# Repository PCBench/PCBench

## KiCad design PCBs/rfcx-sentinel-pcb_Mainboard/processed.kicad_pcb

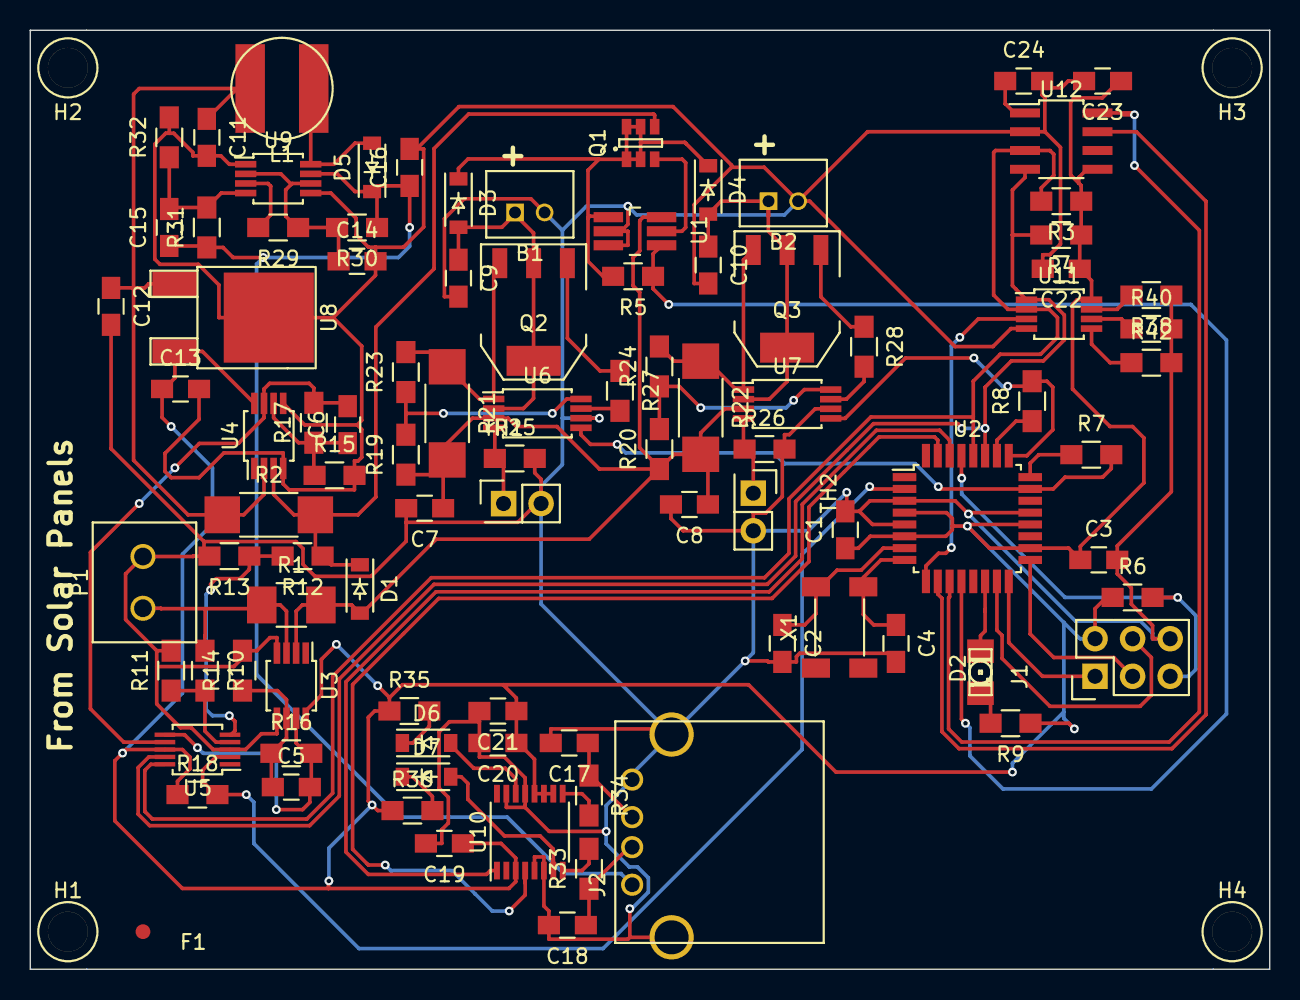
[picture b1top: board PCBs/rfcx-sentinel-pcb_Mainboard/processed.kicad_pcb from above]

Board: 2 copper layers, 83.8 x 63.5 mm, 100 parts (1 on the bottom side), 64 nets.

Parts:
B1, B2: Li-ion(2Cell); JST_BAT
C1, C3, C12, C13, C14: 1uF; C_0805_HandSoldering
C2, C4: 6pF; C_0805_HandSoldering
C5, C6, C7, C8, C9, C10, C22: 0.1uF; C_0805_HandSoldering
C11: 22uF Tant; C_0805_HandSoldering
C15: 39pF; C_0805_HandSoldering
C16: 68uF Tant; C_0805_HandSoldering
C17, C18: 47pF; C_0805_HandSoldering
C19, C20: 100nF; C_0805_HandSoldering
C21: 4.7uF; C_0805_HandSoldering
C23: 0.22uF; C_0805_HandSoldering
C24: 0.1; C_0805_HandSoldering
D1, D3, D4: 1N5819; SOD-123
D2: LED; LED-1206
D5: Diode-Shottky; SOD-123
D6: GRN; SOD-123
D7: LED; SOD-123
F1: Fiducial; Fiducial_1mm_Dia_2.54mm_Outer_CopperTop
H1, H2, H3, H4: Mounting_Hole; Mnt_Hole
J1: ICSP; Pin_Header_Straight_2x03
J2: USB; USB_A
L1: 6.8uH; Ind_6x6
Noname_1: Symbol_OSHW-Logo_SilkScreen
P1: CONN_01X02; TerminalBlock_2
Q1: FDC638; FDC-SOT-23-6
Q2, Q3: FZT788B; SOT-223
R1: Res; R_1210_HandSoldering
R2: 0.5,1W; R_2010_HandSoldering
R3, R4, R6, R18, R19, R20, R38, R40, R42: 10k; R_0805_HandSoldering
R5: 470k; R_0805_HandSoldering
R7, R8, R27, R28: 1k; R_0805_HandSoldering
R9, R35, R36: 730; R_0805_HandSoldering
R10, R12: 1540; R_0805_HandSoldering
R11, R13: 2100; R_0805_HandSoldering
R14, R15, R29: 200k; R_0805_HandSoldering
R16: 2550; R_0805_HandSoldering
R17: Res; R_0805_HandSoldering
R21, R22: 0.2, 1W; R_2010_HandSoldering
R23, R24: 5k; R_0805_HandSoldering
R25, R26, R32: 49.9k; R_0805_HandSoldering
R30: 49.9; R_0805_HandSoldering
R31: 150k; R_0805_HandSoldering
R33, R34: 27; R_0805_HandSoldering
TH1, TH2: NTC; Pin_Header_Straight_2x01
U1: LTC4412; TSOT-6-MK06A_Handsoldering
U2: ATmega328P; TQFP-32_7x7mm_Pitch0.8mm
U3, U4: LTC6800; MSOP-8_3x3mm_Pitch0.65mm
U5: ADS1015; MSOP-10_3x3mm_Pitch0.5mm
U6, U7: bq2057CTS; TSSOP-8_4.4x3mm_Pitch0.65mm
U8: SM72238; DPAK-2
U9: LMR61428; MSOP-8_3x3mm_Pitch0.65mm
U10: FT230X; SSOP-16_3.9x4.9mm_Pitch0.635mm
U11: LM75BDP; MSOP-8_3x3mm_Pitch0.65mm
U12: HIH6130; HIH-SOIC-8
X1: 32kHz; SOJ-4

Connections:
+3V3: C1.1, C3.1, C13.1, C19.1, C20.1, C21.1, C22.1, C23.1, J1.2, R3.1, R4.1, R6.1, R9.1, R18.1, R35.1, R36.1, U2.4, U2.6, U2.18, U2.20, U3.8, U4.8, U5.8, U8.3, U10.3, U10.10, U10.11, U10.12, U11.8, U12.8
+5V: C15.1, C16.1, D5.1, J2.1, R30.1, R31.1, U9.7
/+3.3V and +5V Regulation/LM_FB: C15.2, R31.2, R32.1, U9.4
/ADC/Input-Current-H: P1.1, R1.1, R10.1, U3.3
/ADC/Input-Current-L: C7.1, C8.1, D1.2, R1.2, R19.1, R20.1, R21.2, R22.2, U1.6, U3.2, U6.3, U7.3
/ADC/Output-Current-H: D1.1, Q1.3, R2.2, R12.1, U4.3
/ADC/Output-Current-L: C11.1, C12.1, L1.1, R2.1, U4.2, U8.1
/Battery Management/Battery-Vout: D3.1, D4.1, Q1.1, R5.2, U1.1
/Environment Sensors/ENV_AL_H: U2.11, U12.5
/Environment Sensors/ENV_AL_L: U2.10, U12.6
/Environment Sensors/ENV_OS: U2.9, U11.3
/Microcontroller/AT-Alert: R18.2, U2.2, U5.2
/Microcontroller/AT-BAT1-STAT: R7.2, U2.23, U6.5
/Microcontroller/AT-BAT2-STAT: R8.2, U2.25, U7.5
/Microcontroller/AT-RXD: U2.30, U10.1
/Microcontroller/AT-SCL: R3.2, U2.28, U5.10, U11.2, U12.3
/Microcontroller/AT-SDA: R4.2, U2.27, U5.9, U11.1, U12.4
/Microcontroller/AT-TXD: U2.31, U10.4
/Microcontroller/PPM_STAT: R5.1, U1.4, U2.12
GND: B1.2, B2.2, C1.2, C2.2, C3.2, C4.2, C7.2, C8.2, C9.2, C10.2, C11.2, C12.2, C13.2, C14.2, C16.2, C17.2, C18.2, C19.2, C20.2, C21.2, C22.2, C23.2, C24.2, J1.6, J2.4, J2.5, P1.2, R11.2, R13.2, R14.2, R15.2, R25.2, R26.2, R32.2, R38.1, R40.2, R42.2, TH1.2, TH2.2, U1.2, U1.3, U2.3, U2.5, U2.21, U3.4, U3.5, U4.4, U4.5, U5.3, U6.6, U7.6, U8.2, U9.1, U9.5, U10.5, U10.6, U10.13, U10.15, U11.4, U12.2
unnamed: B1.1, C9.1, D3.2, Q2.2, Q2.4, U6.2
unnamed: B2.1, C10.1, D4.2, Q3.2, Q3.4, U7.2
unnamed: C2.1, U2.7, X1.1
unnamed: C4.1, U2.8, X1.4
unnamed: C5.1, R14.1, R16.1, U3.6
unnamed: C5.2, R16.2, U3.7, U5.6
unnamed: C6.1, R15.1, R17.1, U4.6
unnamed: C6.2, R17.2, U4.7, U5.7
unnamed: C14.1, R29.1, R30.2, U9.2, U9.6
unnamed: C17.1, J2.3, R34.1
unnamed: C18.1, J2.2, R33.1
unnamed: C24.1, U12.1
unnamed: D2.1, R9.2
unnamed: D2.2, U2.14
unnamed: D5.2, L1.2, U9.8
unnamed: D6.1, R35.2
unnamed: D6.2, U10.14
unnamed: D7.1, R36.2
unnamed: D7.2, U10.7
unnamed: J1.1, U2.16
unnamed: J1.3, U2.17
unnamed: J1.4, U2.15
unnamed: J1.5, R6.2, U2.29
unnamed: Q1.2, U1.5
unnamed: Q2.1, R27.1
unnamed: Q2.3, R21.1, R23.2, U6.1
unnamed: Q3.1, R28.1
unnamed: Q3.3, R22.1, R24.2, U7.1
unnamed: R7.1, U2.24
unnamed: R8.1, U2.26
unnamed: R10.2, R11.1, U5.4
unnamed: R12.2, R13.1, U5.5
unnamed: R19.2, R23.1, U6.8
unnamed: R20.2, R24.1, U7.8
unnamed: R25.1, TH1.1, U6.4
unnamed: R26.1, TH2.1, U7.4
unnamed: R27.2, U6.7
unnamed: R28.2, U7.7
unnamed: R29.2, U9.3
unnamed: R33.2, U10.8
unnamed: R34.2, U10.9
unnamed: R38.2, U11.7
unnamed: R40.1, U11.6
unnamed: R42.1, U11.5

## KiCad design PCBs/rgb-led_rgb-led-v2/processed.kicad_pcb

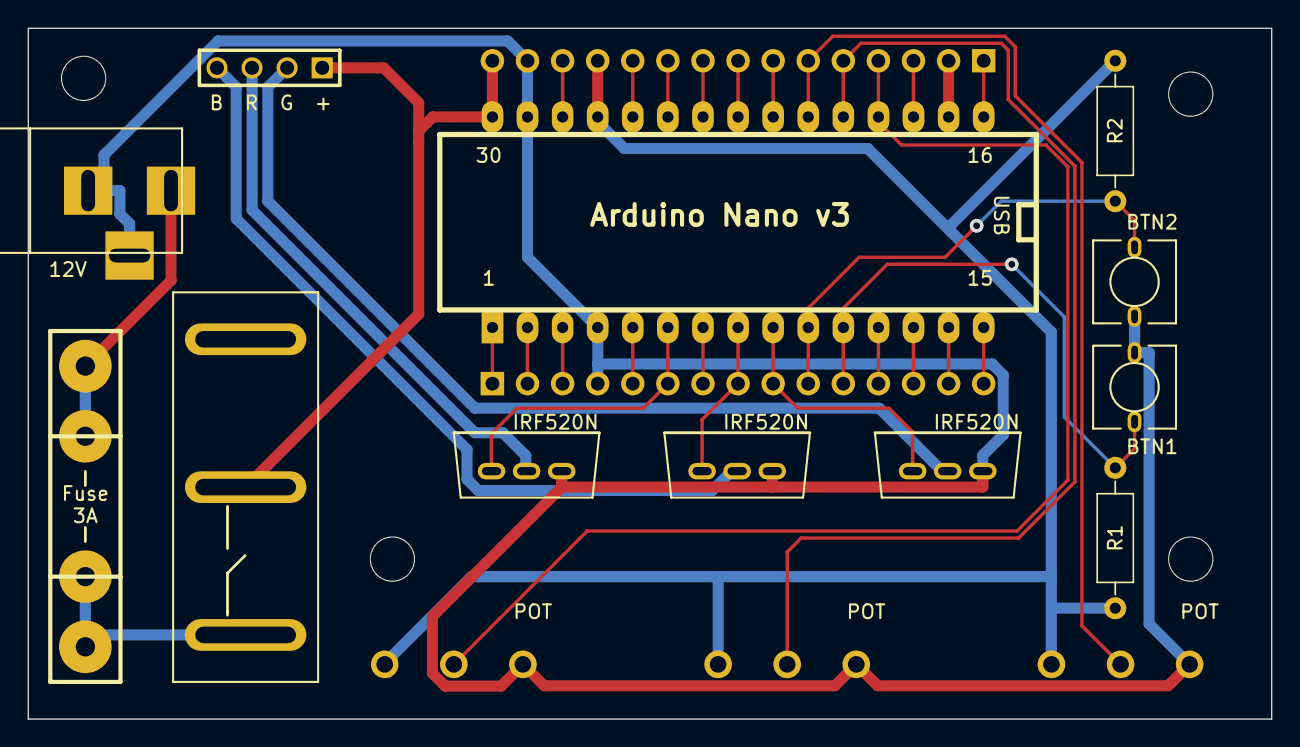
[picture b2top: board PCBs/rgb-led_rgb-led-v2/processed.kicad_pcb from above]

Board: 2 copper layers, 90.0 x 50.0 mm, 17 parts (0 on the bottom side), 34 nets.

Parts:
BTN1, BTN2: SPST; PUSHBUTTON_TS044S
CON1: BARREL_JACK
CONN1: RGB LED; PIN_ARRAY_4x1
F1: FUSE; FUSE5-20
P1, P2: CONN_01X15; Pin_Header_Straight_1x15_Pitch2.54mm_Noborder
QB1: IRF520N FET; IRF520N
QG1: IRF520N FET; IRF520N
QR1: IRF520N FET; IRF520N
R1, R2: R; R_Axial_DIN0207_L6.3mm_D2.5mm_P10.16mm_Horizontal
RV1: POT; POT_3
RV2, RV3: POT; POT_3_Naked
SW1: SPST; KCD3
UC1: ARDUINO_NANO; arduino_nano

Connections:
3.3V: P1.2, UC1.2
5V: P1.12, R1.2, R2.2, RV1.1, RV2.1, RV3.1, UC1.12
A1: P1.1, UC1.1
A3: P1.3, UC1.3
A4: P1.4, RV1.2, UC1.4
A5: P1.5, RV2.2, UC1.5
A6: P1.6, RV3.2, UC1.6
A7: P1.7, UC1.7
A8: P1.8, UC1.8
A9: P1.9, UC1.9
A10: P1.10, UC1.10
A11: P1.11, UC1.11
A13: P1.13, UC1.13
A16: P2.1, UC1.16
A17: P2.2, UC1.17
A18: P2.3, UC1.18
A20: P2.5, UC1.20
A21: P2.6, QR1.G, UC1.21
A22: P2.7, UC1.22
A23: P2.8, QB1.G, UC1.23
A24: P2.9, QG1.G, UC1.24
A25: BTN2.1, P2.10, R2.1, UC1.25
A26: BTN1.1, P2.11, R1.1, UC1.26
A27: P2.12, UC1.27
A28: P2.13, UC1.28
A29: P2.14, UC1.29
A30: P2.15, UC1.30
GND: BTN1.2, BTN2.2, CON1.2, CON1.3, P1.14, P2.4, QB1.S, QG1.S, QR1.S, RV1.3, RV2.3, RV3.3, UC1.14, UC1.19
unnamed: CON1.1, F1.1
unnamed: CONN1.2, QG1.D
unnamed: CONN1.3, QR1.D
unnamed: CONN1.4, QB1.D
unnamed: F1.2, SW1.1
VIN: CONN1.1, P1.15, SW1.2, UC1.15

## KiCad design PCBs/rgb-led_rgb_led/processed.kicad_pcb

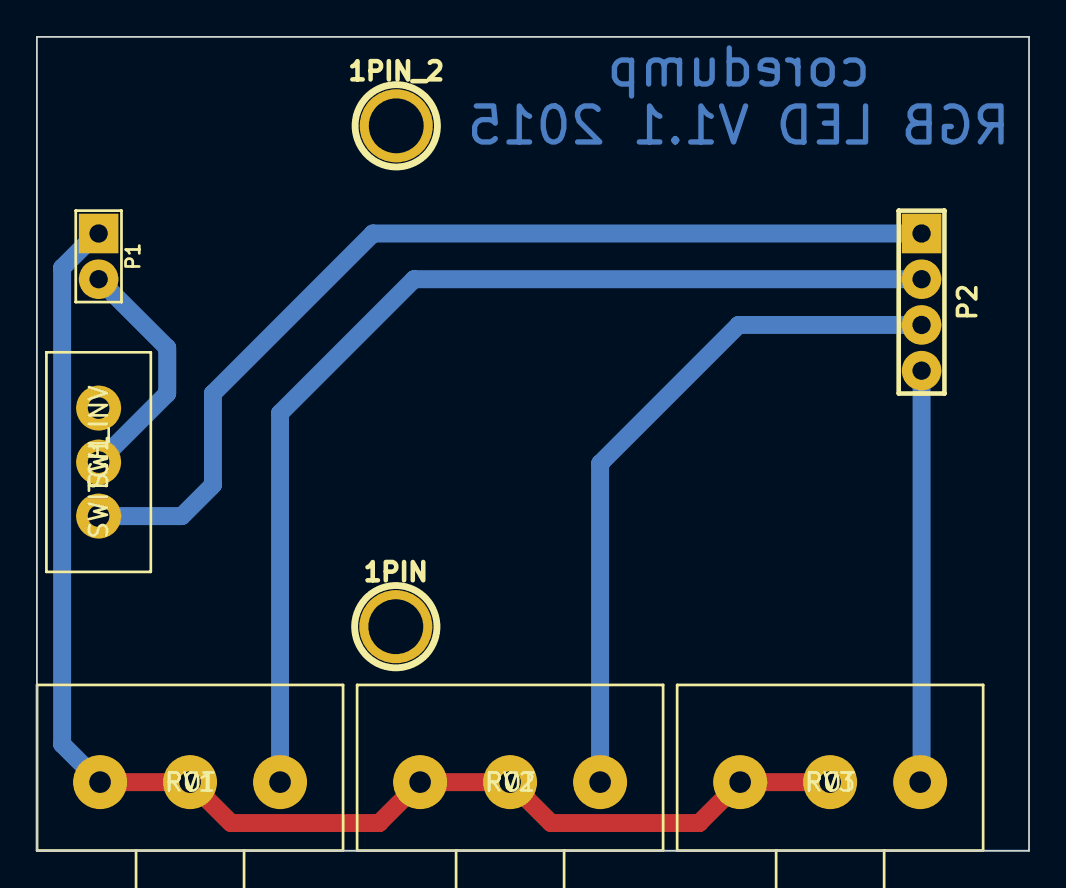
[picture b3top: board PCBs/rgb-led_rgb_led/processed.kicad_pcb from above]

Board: 2 copper layers, 55.1 x 45.2 mm, 9 parts (1 on the bottom side), 6 nets.

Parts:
1PIN, 1PIN_2: P***; 1pin
Noname_1: OSHW_COPPER_10MM
P1: CONN_2; PIN_ARRAY_2X1_THICK
P2: CONN_4; PIN_ARRAY_4x1_THICK
RV1, RV2, RV3: POT; POT_3_THICK
SW1: SWITCH_INV; Switch_SS-12F46

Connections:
GND: P1.1, RV1.1, RV1.2, RV2.1, RV2.2, RV3.1, RV3.2
unnamed: P2.4, RV3.3
unnamed: P2.3, RV2.3
unnamed: P2.2, RV1.3
unnamed: P2.1, SW1.1
VDD: P1.2, SW1.2

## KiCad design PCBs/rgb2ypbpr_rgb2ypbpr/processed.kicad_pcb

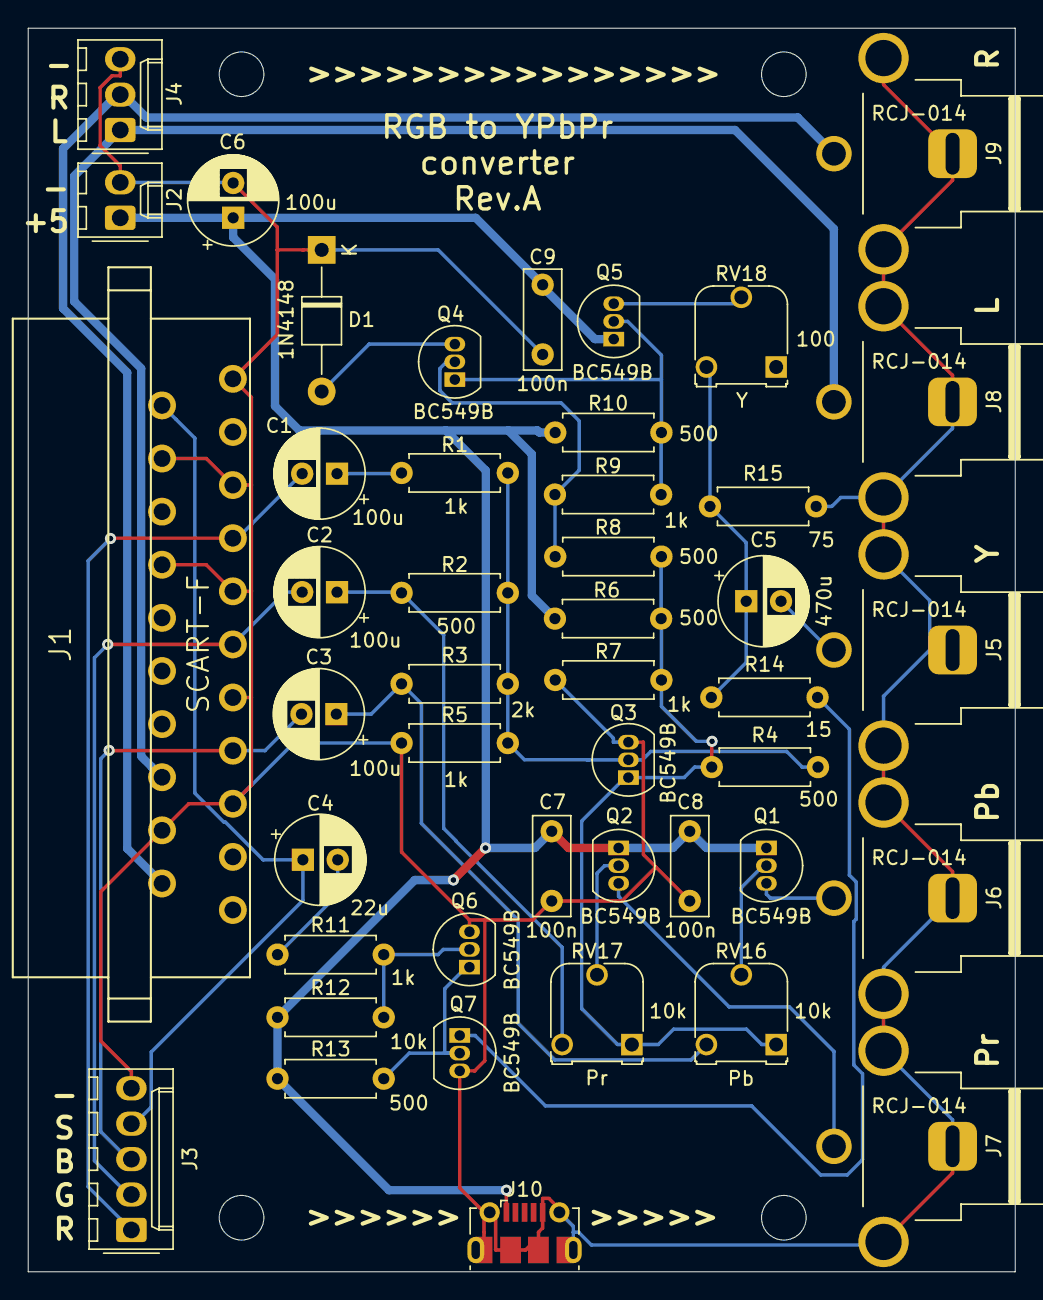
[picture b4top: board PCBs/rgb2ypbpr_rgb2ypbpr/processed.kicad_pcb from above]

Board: 2 copper layers, 70.8 x 89.2 mm, 49 parts (0 on the bottom side), 27 nets.

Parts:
C1, C2, C3, C6: 100u; CP_Radial_D6.3mm_P2.50mm
C4: 22u; CP_Radial_D6.3mm_P2.50mm
C5: 470u; CP_Radial_D6.3mm_P2.50mm
C7, C8, C9: 100n; C_Disc_D7.0mm_W2.5mm_P5.00mm
D1: 1N4148; D_T-1_P10.16mm_Horizontal
H1, H2, H3, H4: MountingHole; MountingHole_3.2mm_M3
J1: SCART-F; SCART
J2: Conn_01x02; Molex_KK-254_AE-6410-02A_1x02_P2.54mm_Vertical
J3: Conn_01x05; Molex_KK-254_AE-6410-05A_1x05_P2.54mm_Vertical
J4: Conn_01x03; Molex_KK-254_AE-6410-03A_1x03_P2.54mm_Vertical
J5, J6, J7, J8, J9: RCJ-014; CUI_RCJ-01X-WIDE
J10: USB_B_Micro; USB_Micro-B_Molex-105017-0001
Q1, Q2, Q3, Q4, Q5, Q6, Q7: BC549B; TO-92_Inline
R1, R5, R7, R9, R11: 1k; R_Axial_DIN0207_L6.3mm_D2.5mm_P7.62mm_Horizontal
R2, R4, R6, R8, R10, R13: 500; R_Axial_DIN0207_L6.3mm_D2.5mm_P7.62mm_Horizontal
R3: 2k; R_Axial_DIN0207_L6.3mm_D2.5mm_P7.62mm_Horizontal
R12: 10k; R_Axial_DIN0207_L6.3mm_D2.5mm_P7.62mm_Horizontal
R14: 15; R_Axial_DIN0207_L6.3mm_D2.5mm_P7.62mm_Horizontal
R15: 75; R_Axial_DIN0207_L6.3mm_D2.5mm_P7.62mm_Horizontal
RV16, RV17: 10k; Potentiometer_Runtron_RM-065_Vertical
RV18: 100; Potentiometer_Runtron_RM-065_Vertical

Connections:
+5V: C6.1, C7.1, C8.1, C9.2, J2.1, J10.1, Q1.1, Q2.1, Q5.1, R6.2, R10.1, R12.2, R13.2
Audio_L: J1.6, J4.1, J8.1
Audio_R: J1.2, J4.2, J9.1
B_IN: C3.2, J1.7, J3.3
CSYNC_IN: C4.1, J1.20, J3.4
GND: C6.2, C7.2, C8.2, C9.1, D1.1, J1.4, J1.5, J1.9, J1.13, J1.14, J1.17, J1.18, J1.21, J2.2, J3.5, J4.3, J5.2, J6.2, J7.2, J8.2, J9.2, J10.5, J10.6, Q3.3, Q6.3, Q7.3, R5.2, R7.1, R15.2
G_IN: C2.2, J1.11, J3.2
unnamed: C1.1, R1.2
unnamed: C2.1, R2.2, RV17.3
unnamed: C3.1, R3.2, RV16.3
unnamed: C4.2, R11.2
unnamed: C5.1, R14.1, R15.1, RV18.3
unnamed: D1.2, Q4.3
unnamed: Q1.2, RV16.2
unnamed: Q2.2, RV17.2
unnamed: Q3.1, R4.2, R6.1, R7.2, R8.2, RV16.1, RV17.1
unnamed: Q3.2, R1.1, R2.1, R3.1, R4.1, R5.1
unnamed: Q4.1, Q5.2, R9.1, R10.2
unnamed: Q4.2, R8.1, R9.2
unnamed: Q5.3, RV18.2
unnamed: Q6.1, Q7.2, R13.1
unnamed: Q6.2, R11.1, R12.1
unnamed: Q7.1, R14.2
Pb_OUT: J6.1, Q1.3
Pr_OUT: J7.1, Q2.3
R_IN: C1.2, J1.15, J3.1
Y_OUT: C5.2, J5.1

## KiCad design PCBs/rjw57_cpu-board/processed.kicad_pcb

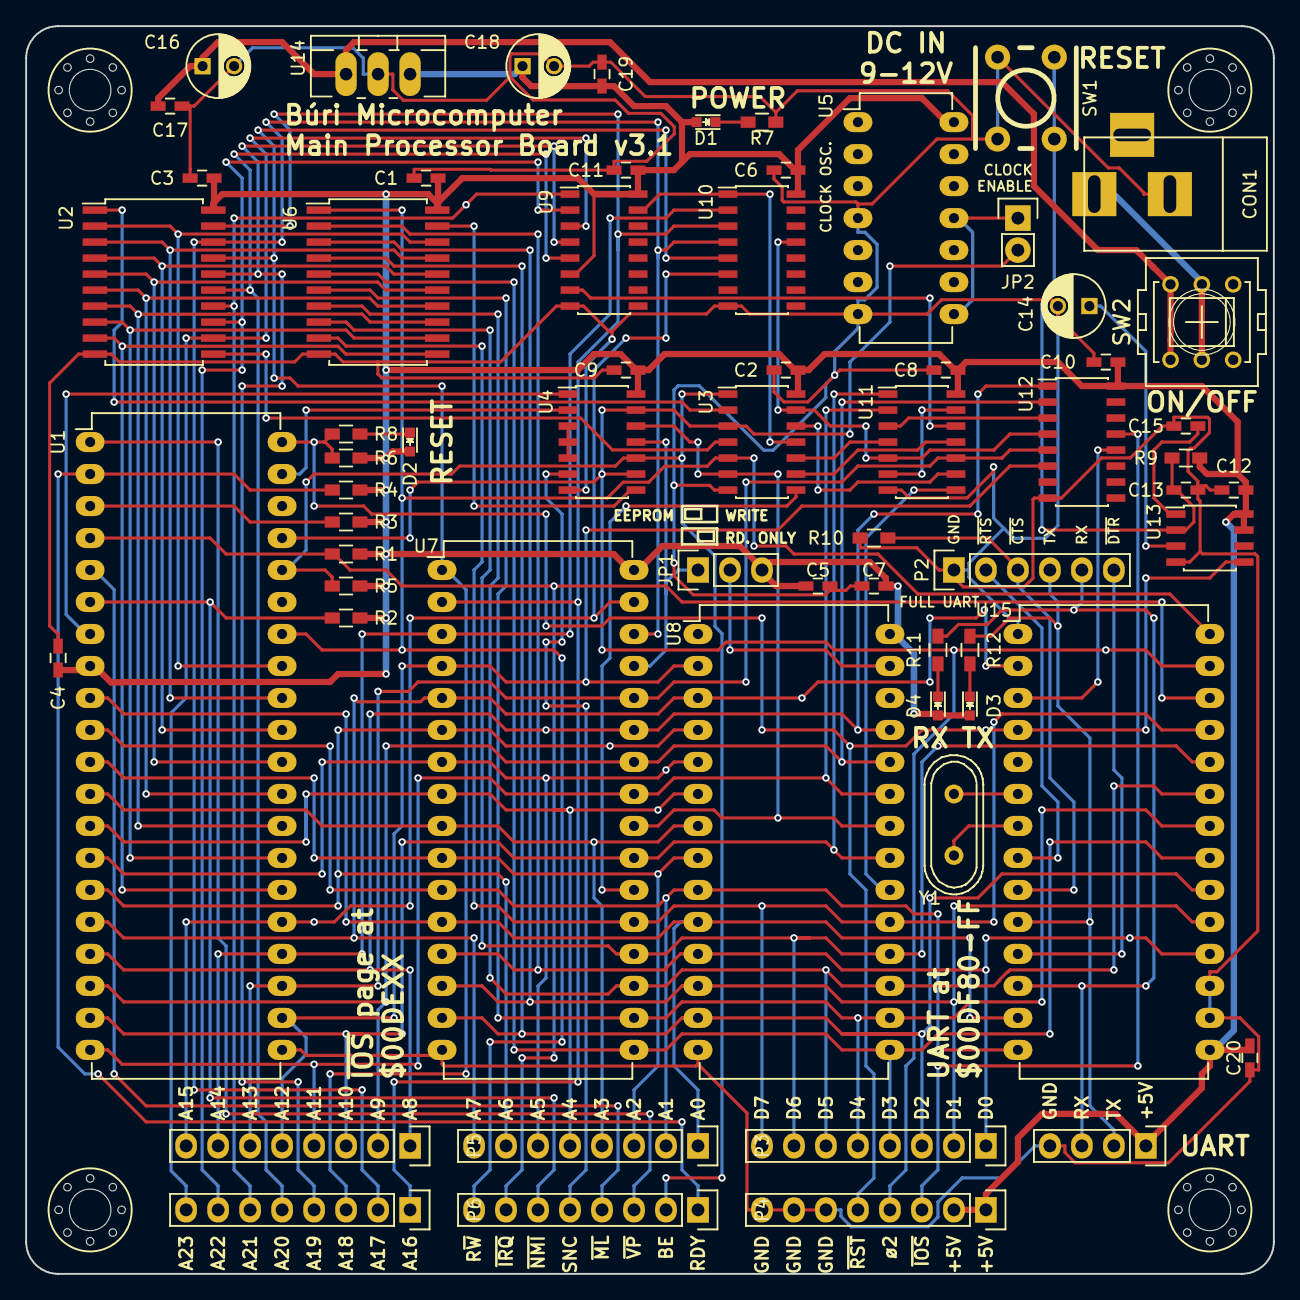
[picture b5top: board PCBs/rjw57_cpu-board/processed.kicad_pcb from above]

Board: 2 copper layers, 99.1 x 99.1 mm, 69 parts (0 on the bottom side), 91 nets.

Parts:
C1, C2, C3, C4, C5, C6, C7, C8, C9, C10, C11, C12, C13, C15, C17, C19, C20: 100n; C_0603_HandSoldering
C14, C16, C18: 1µ; C_Radial_D5_L6_P2.5
CON1: POWER_IN; BARREL_JACK
D1: PWR; LED_0603
D2: RST; LED_0603
D3: TX; LED_0603
D4: RX; LED_0603
JP1: ROMWRITE; Pin_Header_Straight_1x03
JP2: Jumper_NC_Small; Pin_Header_Straight_1x02
P1: D0..D7; Pin_Header_Straight_1x08
P2: UART; Pin_Header_Straight_1x06
P3: A0..A7; Pin_Header_Straight_1x08
P4: CTRL1; Pin_Header_Straight_1x08
P5: A8..A15; Pin_Header_Straight_1x08
P6: A16..A23; Pin_Header_Straight_1x08
P7: CTRL2; Pin_Header_Straight_1x08
P8: UARTMINI; Pin_Header_Straight_1x04
R1, R2, R3, R4, R5, R6, R7, R8, R9, R10, R11, R12: 330; R_0603_HandSoldering
SW1: RESET; SW_M6_PTH
SW2: ON/OFF; switch-misc-PVA2R
U1: W65C816; DIP-40_W15.24mm_LongPads
U2: 74HC573; SOIC-20_7.5x12.8mm_Pitch1.27mm
U3: 74HC04; SOIC-14_3.9x8.7mm_Pitch1.27mm
U4, U11: 74HC00; SOIC-14_3.9x8.7mm_Pitch1.27mm
U5: CLOCK; DIP-14_W7.62mm_LongPads
U6: 74HC245; SOIC-20_7.5x12.8mm_Pitch1.27mm
U7: AS6C4008; DIP-32_W15.24mm_LongPads
U8: AT28C64B; DIP-28_W15.24mm_LongPads
U9, U10, U12: 74HC138; SOIC-16_3.9x9.9mm_Pitch1.27mm
U13: TL7705A; SOIC-8_3.9x4.9mm_Pitch1.27mm
U14: 7805; TO-220_Neutral123_Vertical_LargePads
U15: W65C51; DIP-28_W15.24mm_LongPads
W1, W2, W3, W4: MOUNTING; M3_MOUNT
Y1: 1.8432M; Crystal_HC49-U_Vertical

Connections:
+5V: C1.1, C2.1, C3.1, C4.1, C5.1, C6.1, C7.1, C8.1, C9.1, C10.1, C11.1, C12.1, C18.1, C19.1, C20.1, D1.2, D2.2, D3.2, D4.2, JP1.3, P7.1, P7.2, P8.1, R1.1, R2.1, R3.1, R4.1, R5.1, R6.1, R9.1, U1.8, U2.20, U3.14, U4.14, U5.14, U6.20, U7.32, U8.28, U9.6, U9.16, U10.16, U11.14, U12.16, U13.7, U13.8, U14.3, U15.15
/A2: P3.3, U1.11, U7.10, U8.8
/A3: P3.4, U1.12, U7.9, U8.7
/A4: P3.5, U1.13, U7.8, U8.6
/A5: P3.6, U1.14, U7.7, U8.5
/A6: P3.7, U1.15, U7.6, U8.4
/ACIA/CS0: P3.8, U1.16, U7.5, U8.3, U15.2
/ACIA/D0: P1.1, U6.2, U7.13, U8.11, U15.18
/ACIA/D1: P1.2, U6.3, U7.14, U8.12, U15.19
/ACIA/D2: P1.3, U6.4, U7.15, U8.13, U15.20
/ACIA/D3: P1.4, U6.5, U7.17, U8.15, U15.21
/ACIA/D4: P1.5, U6.6, U7.18, U8.16, U15.22
/ACIA/D5: P1.6, U6.7, U7.19, U8.17, U15.23
/ACIA/D6: P1.7, U6.8, U7.20, U8.18, U15.24
/ACIA/D7: P1.8, U6.9, U7.21, U8.19, U15.25
/ACIA/PHI2: JP2.2, P7.4, U1.37, U3.3, U4.9, U4.13, U15.27
/ACIA/R/~W: P4.8, U1.34, U3.5, U6.1, U15.28
/ACIA/RS0: P3.1, U1.9, U7.12, U8.10, U15.13
/ACIA/RS1: P3.2, U1.10, U7.11, U8.9, U15.14
/ACIA/RX: P2.5, P8.3, R12.2, U15.12
/ACIA/TX: P2.4, P8.2, R11.2, U15.10
/ACIA/~CS1: U12.12, U15.3
/ACIA/~CTS: P2.3, R10.1, U15.9
/ACIA/~DTR: P2.6, U15.11
/ACIA/~IRQ: P4.7, R1.2, U1.4, U15.26
/ACIA/~RTS: P2.2, U15.8
/Address decode/A8: P5.1, U1.17, U7.27, U8.25, U12.1
/Address decode/A9: P5.2, U1.18, U7.26, U8.24, U12.2
/Address decode/A10: P5.3, U1.19, U7.23, U8.21, U11.1
/Address decode/A11: P5.4, U1.20, U7.25, U8.23, U11.2
/Address decode/A12: P5.5, U1.22, U7.4, U8.2, U12.6
/Address decode/A13: P5.6, U1.23, U7.28, U11.10, U12.5
/Address decode/A14: P5.7, U1.24, U7.3, U10.2
/Address decode/A15: P5.8, U1.25, U7.31, U10.6
/Address decode/A16: P6.1, U2.19, U7.2, U10.3
/Address decode/A17: P6.2, U2.18, U7.30, U10.4
/Address decode/A18: P6.3, U2.17, U7.1, U10.5
/Address decode/A19: P6.4, U2.16, U9.4
/Address decode/A20: P6.5, U2.15, U9.5
/Address decode/A21: P6.6, U2.14, U9.1
/Address decode/A22: P6.7, U2.13, U9.2
/Address decode/A23: P6.8, U2.12, U9.3
/Address decode/LOADDR: U3.10, U11.4
/Address decode/RAMHOLE: U3.12, U11.9
/Address decode/RAMSEL: U3.9, U11.11
/Address decode/~HIADDR: U9.7, U11.12
/Address decode/~IO2: P7.3, U12.13
/Address decode/~LOADDR: U3.11, U9.15, U10.1
/Address decode/~LORAM: U11.6, U11.13
/Address decode/~RAMHOLE: U3.13, U10.13, U11.5, U12.4
/Address decode/~ROMSEL: U8.20, U11.8
/BA0: U1.33, U2.2, U6.18
/BA1: U1.32, U2.3, U6.17
/BA2: U1.31, U2.4, U6.16
/BA3: U1.30, U2.5, U6.15
/BA4: U1.29, U2.6, U6.14
/BA5: U1.28, U2.7, U6.13
/BA6: U1.27, U2.8, U6.12
/BA7: U1.26, U2.9, U6.11
/BE: P4.2, R5.2, U1.36, U3.1, U4.10
/RDY: P4.1, R4.2, U1.2
/Reset & power/~RESET: P7.5, R6.2, R8.2, U1.40, U13.5, U15.4
/SYNC: P4.5, U4.6
/VDA: U1.39, U4.2
/VPA: U1.7, U4.1
/~ABORT: R3.2, U1.3
/~MEMWE: JP1.1, U4.11, U7.29
/~ML: P4.4, U1.5
/~NMI: P4.6, R2.2, U1.6
/~RAMSEL: U3.8, U7.22
/~ROMWE: JP1.2, U8.27
/~R~/W: U3.6, U4.12, U7.24, U8.22
/~VP: P4.3, U1.1
GND: C1.2, C2.2, C3.2, C4.2, C5.2, C6.2, C7.2, C8.2, C9.2, C10.2, C11.2, C12.2, C13.2, C14.2, C15.2, C16.2, C17.2, C18.2, C19.2, C20.2, CON1.2, P2.1, P7.6, P7.7, P7.8, P8.4, R7.1, R10.2, SW1.1, U1.21, U2.10, U3.7, U4.7, U5.4, U5.7, U6.10, U7.16, U8.14, U9.8, U10.8, U11.7, U12.8, U13.4, U14.2, U15.1, U15.16, U15.17
unnamed: C13.1, R9.2, SW1.2, U13.2
unnamed: C14.1, U13.3
unnamed: C15.1, U13.1
unnamed: C16.1, C17.1, SW2.1, SW2.4, U14.1
unnamed: CON1.1, SW2.2, SW2.5
unnamed: D1.1, R7.2
unnamed: D2.1, R8.1
unnamed: D3.1, R11.1
unnamed: D4.1, R12.1
unnamed: JP2.1, U5.8, U5.11
unnamed: U2.1, U3.2
unnamed: U2.11, U3.4
unnamed: U4.3, U4.4, U4.5
unnamed: U4.8, U6.19
unnamed: U11.3, U12.3
unnamed: U15.6, Y1.1
unnamed: U15.7, Y1.2

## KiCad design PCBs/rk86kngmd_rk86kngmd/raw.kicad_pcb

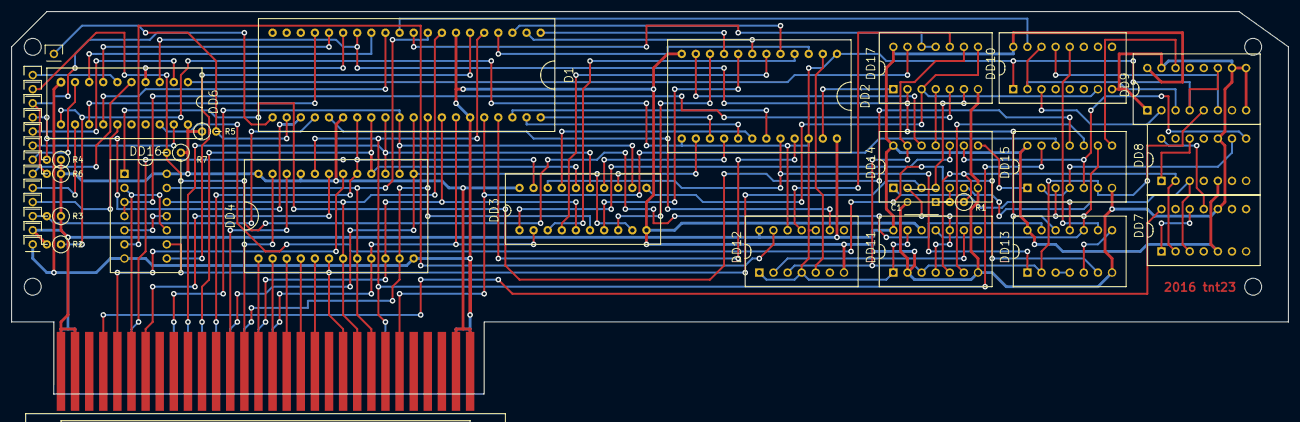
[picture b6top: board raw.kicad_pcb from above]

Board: 2 copper layers, 226.2 x 67.8 mm, 39 parts (0 on the bottom side), 101 nets.

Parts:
C1: 100; C_Disc_D6_P5
D1: К580ВВ55; DIP40-2.5mm
DD2: К555ИР13; DIP24-2.5mm
DD3: К555ИР23; DIP20-2.5mm
DD4: 2716; DIP24-2.5mm
DD6: К555ИР22; DIP20-2.5mm
DD7, DD8: К555ИЕ5; DIP14-2.5mm
DD9: К555ИЕ7; DIP16-2.5mm
DD10: К555ИД4; DIP16-2.5mm
DD11, DD12: К555ТМ2; DIP14-2.5mm
DD13: К555ЛА3; DIP14-2.5mm
DD14: К555ЛН1; DIP14-2.5mm
DD15: К555ЛИ1; DIP14-2.5mm
DD16: К555ЛЛ1; DIP14-2.5mm
DD17: К555ЛЕ1; DIP14-2.5mm
P1: GND; Pin_Header_Straight_1x01
P2: +5V; Pin_Header_Straight_1x01
P3: IP; Pin_Header_Straight_1x01
P4: DISC_A; Pin_Header_Straight_1x01
P5: DISC_B; Pin_Header_Straight_1x01
P6: DIR; Pin_Header_Straight_1x01
P7: STEP; Pin_Header_Straight_1x01
P8: WR_DATA; Pin_Header_Straight_1x01
P9: WR_GATE; Pin_Header_Straight_1x01
P10: TR00; Pin_Header_Straight_1x01
P11: WPRT; Pin_Header_Straight_1x01
P12: RD_DATA; Pin_Header_Straight_1x01
P13: SIDE; Pin_Header_Straight_1x01
P14: READY; Pin_Header_Straight_1x01
R1: 200; Resistor_Vertical_RM2_5mm
R2, R3, R4, R5, R6, R7: 1K; Resistor_Vertical_RM2_5mm
X1: ОНп-КС-23

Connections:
+5V: D1.26, DD2.24, DD3.20, DD4.21, DD4.24, DD6.20, DD7.5, DD8.5, DD9.16, DD10.16, DD11.14, DD12.14, DD13.14, DD14.14, DD15.14, DD16.14, DD17.14, P2.1, R2.2, R3.1, R4.1, R5.1, R6.1, R7.1, X1.B1, X1.B2, X1.B29, X1.B30
/17: DD2.11, DD14.12
/18: DD3.1, DD14.10
/A0: D1.9, DD4.8, DD16.13, X1.B8
/A1: D1.8, DD4.7, DD16.12, X1.B9
/A2: DD4.6, DD14.3, DD16.9, X1.B10
/A3: DD4.5, X1.B12
/A4: DD4.4, X1.B13
/A5: DD4.3, X1.B14
/A6: DD4.2, X1.B15
/A7: DD4.1, X1.B16
/A8: DD4.23, X1.B17
/A9: DD4.22, X1.B18
/A10: DD4.19, X1.B24
/CS1: DD4.18, X1.B26
/CS3: DD16.2, DD16.10, X1.B25
/D0: D1.34, DD3.2, DD4.9, X1.A15
/D1: D1.33, DD3.5, DD4.10, X1.A16
/D2: D1.32, DD3.6, DD4.11, X1.A17
/D3: D1.31, DD3.9, DD4.13, X1.A18
/D4: D1.30, DD3.12, DD4.14, X1.A22
/D5: D1.29, DD3.15, DD4.15, X1.A21
/D6: D1.28, DD3.16, DD4.16, X1.A20
/D7: D1.27, DD3.19, DD4.17, X1.A19
/OSC: DD7.14, X1.B27
/PB7: D1.25, DD12.9
/PC1: D1.15, DD6.4
/PC2: D1.16, DD6.7
/PC3: D1.17, DD6.13
/PC4: D1.13, DD6.8
/PC5: D1.12, DD6.14
/PC6: D1.11, DD10.15
/PC7: D1.10, DD17.11, DD17.12
/RD: D1.5, DD4.20, DD15.13, X1.A7
/WR: D1.36, DD15.12, X1.B6
/WRDATA: DD6.18, DD13.6
/WRGATE: D1.14, DD6.3, DD13.12, DD17.2
DIR: DD6.5, P6.1
DISC_A: DD6.15, P4.1
DISC_B: DD6.12, P5.1
GND: C1.2, D1.7, D1.35, DD2.12, DD3.10, DD4.12, DD6.10, DD7.10, DD8.10, DD9.1, DD9.8, DD9.9, DD9.10, DD9.15, DD10.8, DD11.2, DD11.7, DD11.12, DD12.7, DD13.7, DD14.7, DD15.7, DD16.7, DD17.7, P1.1, X1.A1, X1.A2, X1.A29, X1.A30
IP: D1.24, P3.1, R3.2
unnamed: C1.1, DD14.5, R1.2
unnamed: D1.1, DD2.9
unnamed: D1.2, DD2.7
unnamed: D1.3, DD2.5
unnamed: D1.4, DD2.3
unnamed: D1.6, DD16.8
unnamed: D1.37, DD2.21
unnamed: D1.38, DD2.19
unnamed: D1.39, DD2.17
unnamed: D1.40, DD2.15
unnamed: DD2.4, DD3.3
unnamed: DD2.6, DD3.4
unnamed: DD2.8, DD3.7
unnamed: DD2.10, DD3.8
unnamed: DD2.14, DD3.13
unnamed: DD2.16, DD3.14
unnamed: DD2.18, DD3.17
unnamed: DD7.1, DD7.12
unnamed: DD7.11, DD8.14
unnamed: DD8.1, DD8.12
unnamed: DD2.1, DD2.13, DD2.22, DD6.11, DD9.4, DD9.11, DD10.1, DD11.1, DD11.13, DD12.1, DD12.4, DD12.10, DD12.12, R2.1
unnamed: DD9.2, DD10.3
unnamed: DD3.11, DD10.7, DD17.3, DD17.8
unnamed: DD10.12, DD13.9
unnamed: DD9.6, DD10.13
unnamed: DD9.3, DD10.2, DD10.14
unnamed: DD9.5, DD11.3, DD12.3, DD13.2, DD14.13, DD15.6, DD17.9
unnamed: DD7.2, DD8.2, DD11.5, R1.1
unnamed: DD11.6, DD15.10
unnamed: DD11.9, DD12.2
unnamed: DD11.4, DD11.10, DD14.2
unnamed: DD11.11, DD13.10, DD15.3, DD15.9
unnamed: DD2.2, DD12.5
unnamed: DD12.11, DD17.10
unnamed: DD12.13, DD16.6
unnamed: DD2.20, DD3.18, DD13.1
unnamed: DD13.3, DD13.4
unnamed: DD13.5, DD13.8
unnamed: DD13.11, DD14.1
unnamed: DD14.4, DD17.6
unnamed: DD7.3, DD8.3, DD14.6
unnamed: DD14.8, DD15.1
unnamed: DD8.8, DD14.9, DD15.5
unnamed: DD14.11, DD17.4
unnamed: DD8.9, DD15.2, DD15.4
unnamed: DD9.14, DD15.8
unnamed: DD15.11, DD16.1
unnamed: DD16.3, DD16.4, DD17.5
unnamed: DD16.5, DD16.11
unnamed: DD2.23, DD17.1
unnamed: DD6.1, DD17.13
RD_DATA: DD13.13, P12.1, R7.2
READY: D1.22, P14.1, R5.2
SIDE: DD6.6, P13.1
STEP: DD6.9, P7.1
TR00: D1.23, P10.1, R4.2
WPRT: D1.21, P11.1, R6.2
WR_DATA: DD6.19, P8.1
WR_GATE: DD6.2, P9.1

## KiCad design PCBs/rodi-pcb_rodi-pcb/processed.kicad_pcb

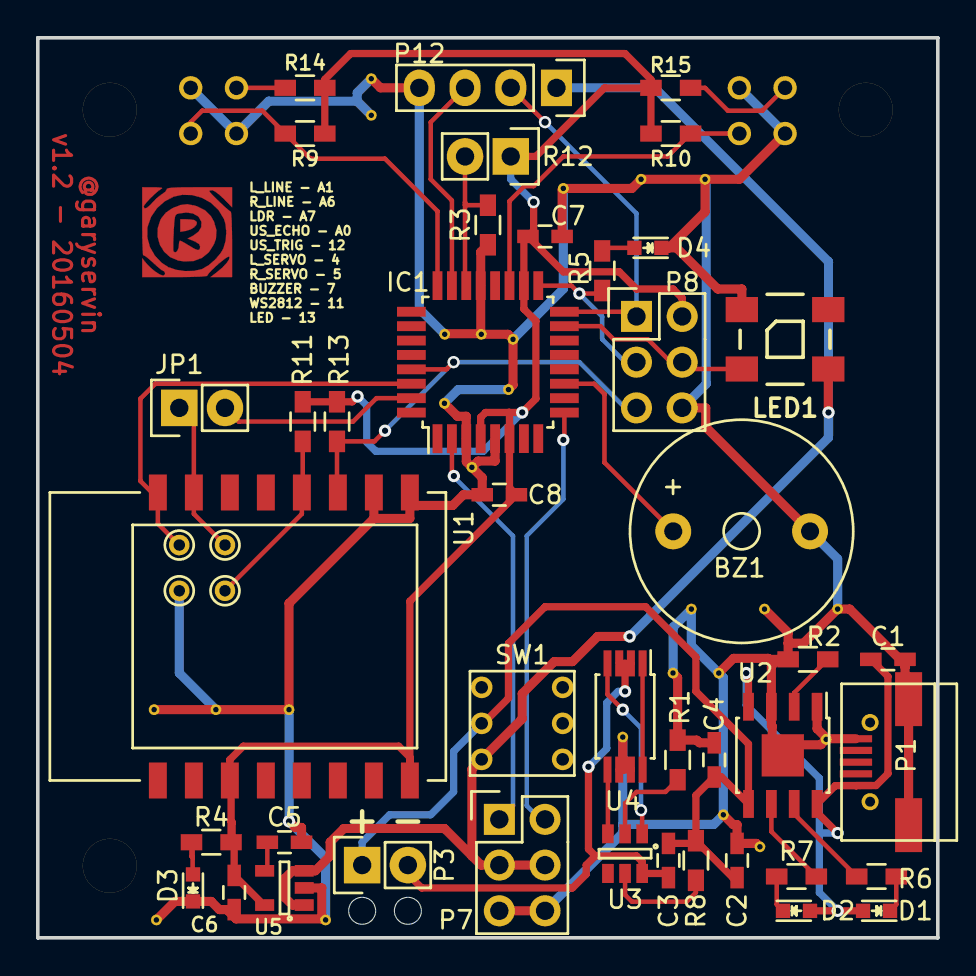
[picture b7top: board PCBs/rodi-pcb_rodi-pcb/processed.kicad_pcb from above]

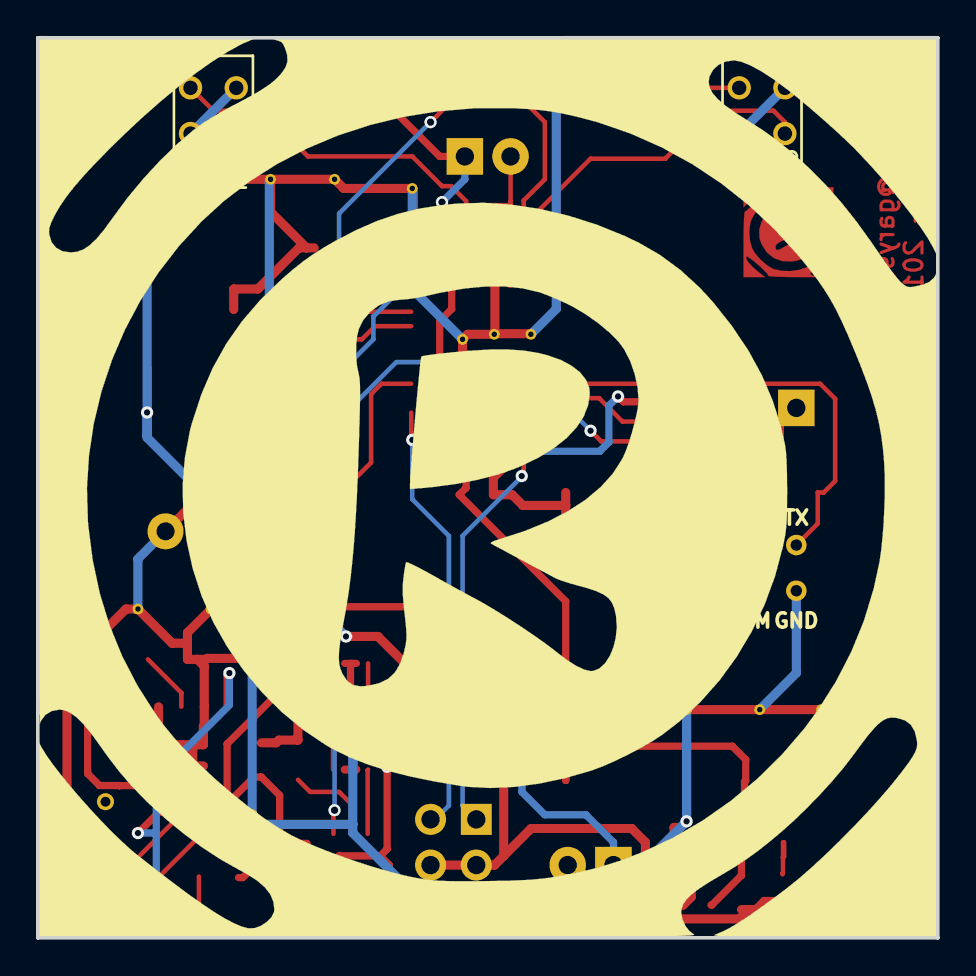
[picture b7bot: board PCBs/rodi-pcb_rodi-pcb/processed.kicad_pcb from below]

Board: 2 copper layers, 50.0 x 50.0 mm, 48 parts (2 on the bottom side), 36 nets.

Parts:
BZ1: BUZZER; Buzzer_12x9.5RM7.6
C1, C2: 10u; C_0603_HandSoldering
C3, C5, C7, C8: 100n; C_0603_HandSoldering
C4, C6: 1u; C_0603_HandSoldering
D1: CHRG; LED-0603
D2: STDBY; LED-0603
D3: PWR; LED-0603
D4: L13; LED-0603
IC1: ATMEGA328P-A; TQFP-32_7x7mm_Pitch0.8mm
JP1: ESP_RX; Pin_Header_Straight_1x02
LED1: WS2812B
P1: USB_OTG; USB_Micro-B
P2, P4, P5, P6: TST; PINTST
P3: BATT; Pin_Header_Straight_1x02
P7: CONN_02X03; Pin_Header_Straight_2x03
P8: ICSP; Pin_Header_Straight_2x03
P12: US1; Pin_Header_Straight_1x04
QRD1: L_LINE; QRD1114
QRD2: R_LINE; QRD1114
R1, R3, R4, R5, R6, R7: 1K; R_0603_HandSoldering
R2: 1K2; R_0603_HandSoldering
R8: 100; R_0603_HandSoldering
R9, R10, R11, R13: 10K; R_0603_HandSoldering
R12: LDR; Pin_Header_Straight_1x02
R14, R15: 220; R_0603_HandSoldering
SW1: ON_OFF; SW_DPDT_5.8
U1: ESP8266-07; ESP8266_ESP-07
U2: TP4056; SOIC-8-1EP_3.9x4.9mm_Pitch1.27mm
U3: DW01-G; SOT-23-6
U4: FS8205; TSSOP-8_4.4x3mm_Pitch0.65mm
U5: SGM2019; SOT-23-5

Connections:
+3V3: C6.1, C7.1, C8.1, IC1.4, IC1.6, IC1.18, P8.2, R4.1, R9.2, R10.2, R11.1, R12.1, R13.1, R14.1, R15.1, U1.11, U1.16, U5.5
+5V: C1.1, D1.2, D2.2, P1.1, U2.4, U2.8
+BATT: C2.1, C3.1, C4.1, P3.1, R8.1, SW1.5, U2.5
BUZZER: BZ1.1, IC1.11
ECHO_US1: IC1.23, P12.3
GND: BZ1.2, C1.2, C2.2, C4.2, C5.2, C6.2, C7.2, C8.2, D3.1, D4.1, IC1.3, IC1.5, IC1.21, LED1.3, P1.5, P1.6, P6.1, P7.5, P7.6, P8.6, P12.4, QRD1.E, QRD1.K, QRD2.E, QRD2.K, R1.2, R2.2, R3.2, U1.1, U1.2, U2.1, U2.3, U2.9, U4.6, U4.7, U5.2
GNDA: C3.2, P3.2, U3.6, U4.2, U4.3
LDR_SENSOR: IC1.22, R3.1, R12.2
L_LINE: IC1.24, QRD1.C, R9.1
L_SERVO: IC1.2, P7.1
MISO: IC1.16, P8.1, P12.2
MOSI: IC1.15, LED1.4, P8.4
unnamed: C5.1, U5.4
unnamed: D1.1, R6.1
unnamed: D2.1, R7.1
unnamed: D3.2, R4.2
unnamed: D4.2, R5.2
unnamed: QRD1.A, R14.2
unnamed: QRD2.A, R15.2
unnamed: R1.1, U3.2
unnamed: R2.1, U2.2
unnamed: R6.2, U2.7
unnamed: R7.2, U2.6
unnamed: R8.2, U3.5
unnamed: U4.1, U4.8
OC: U3.3, U4.5
OD: U3.1, U4.4
PGM_ESP: P2.1, R11.2, U1.4
RESET: IC1.29, P8.5, R13.2, U1.3
RXD: IC1.30, P5.1, U1.8
R_LINE: IC1.19, QRD2.C, R10.1
R_SERVO: IC1.9, P7.2
SCK: IC1.17, P8.3, R5.1
TXD: IC1.31, JP1.2
URXD_ESP: JP1.1, P4.1, U1.7
VDD: LED1.1, P7.3, P7.4, P12.1, SW1.6, U5.1, U5.3

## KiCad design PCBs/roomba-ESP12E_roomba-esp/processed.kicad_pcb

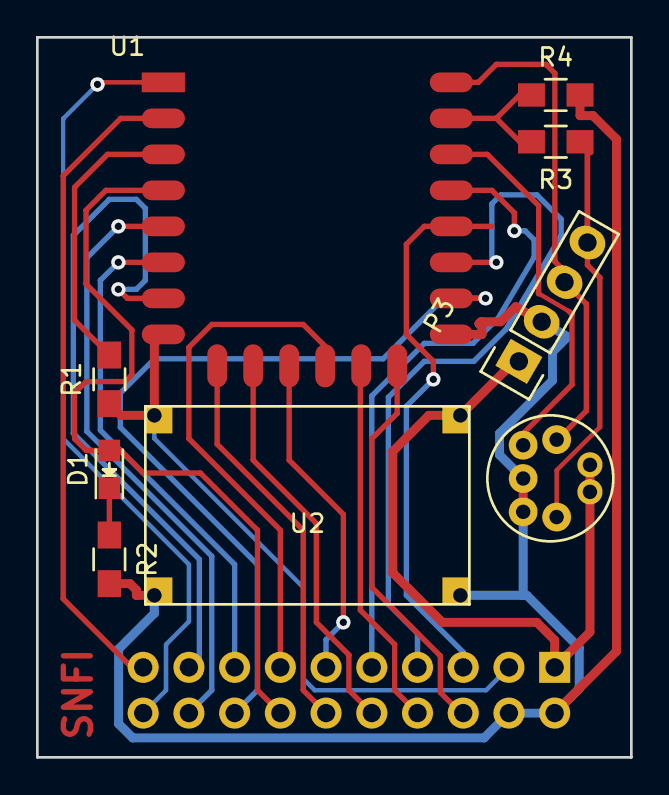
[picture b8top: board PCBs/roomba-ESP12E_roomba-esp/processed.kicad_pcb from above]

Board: 2 copper layers, 33.0 x 40.0 mm, 10 parts (1 on the bottom side), 25 nets.

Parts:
D1: LED; LED-0805
P1: CONN_01X07; mini_DIN_7
P2: CONN_02X10; Socket_Strip_Angled_2x10
P3: CONN_01X04; Socket_Strip_Straight_1x04
R1, R4: 10K; R_0805_HandSoldering
R2: 1K; R_0805_HandSoldering
R3: 5K; R_0805_HandSoldering
U1: ESP-12E
U2: LM2596_module

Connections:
/ADC: P2.19, U1.2
/CS0: P2.12, U1.9
/DD: P1.5, U1.20
/GPIO0: P2.5, U1.18
/GPIO2: P2.7, U1.17
/GPIO5: P2.9, U1.19
/GPIO9: P2.11, U1.11
/GPIO10: P2.13, U1.12
/GPIO12: P2.15, U1.6
/GPIO13: P2.17, U1.7
/GPIO14: P2.18, U1.5
/GPIO15: P2.16, U1.16
/GPIO16: D1.2, P2.14, U1.4
/MISO: P2.10, U1.10
/MOSI: P2.8, U1.13
/RESET: P2.20, U1.1
/RX: R3.2, R4.1, U1.21
/RX_R: P1.3, P3.3, U1.22
/SCK: P2.6, U1.14
/TX_R: P1.4, P3.4, R3.1
/VBat: P1.1, P1.2, P2.1, P3.1, U2.4
GND: P1.6, P1.7, P2.2, P2.4, P3.2, R2.2, R4.2, U1.15, U2.2, U2.3
unnamed: D1.1, R2.1
unnamed: R1.2, U1.3
VCC: P2.3, R1.1, U1.8, U2.1

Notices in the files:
PCBs/rjw57_cpu-board/processed.kicad_pcb:
©2016 Rich Wareham
CC BY-NC-SA 4.0
